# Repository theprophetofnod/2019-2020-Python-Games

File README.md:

# 2019-2020-Python-Games
# Ian started this on 1/15/2019. The end date should be 1/15/2020. If any one finds this after that date please terminate this repositories

# Example Code - Is the code that I am using to learn Python

# CorwRath - Is the name of the finsh product of my game.

# Test Code - Is the unfinshed code that I am working on.

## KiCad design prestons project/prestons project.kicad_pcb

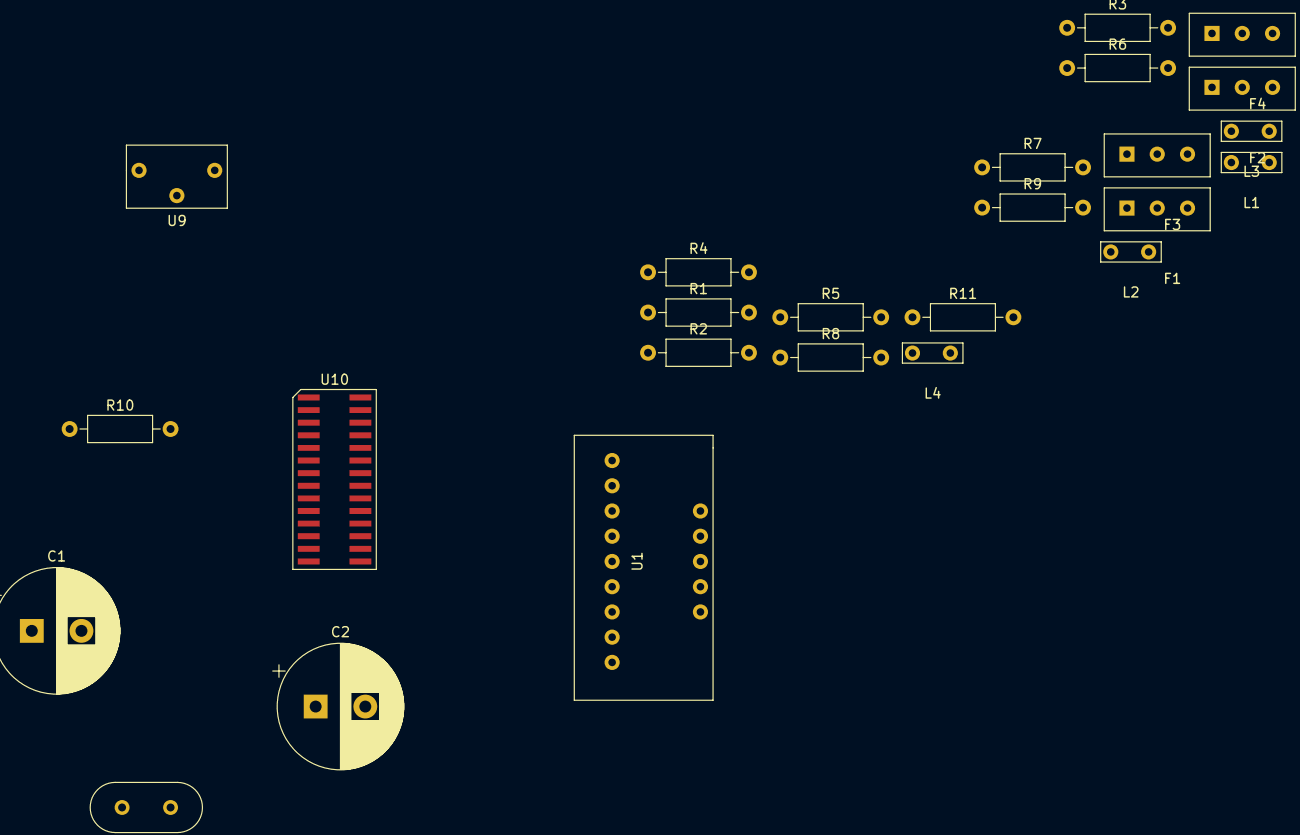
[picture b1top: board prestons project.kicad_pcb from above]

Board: 2 copper layers, 25 parts (0 on the bottom side), 22 nets, no tracks yet.

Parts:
C1: 18pF; CP_Radial_D12.5mm_P5.00mm
C2: 18Pf; CP_Radial_D12.5mm_P5.00mm
F1, F2, F3, F4: FQP30N06L; gatway_switch
L1, L2, L3, L4: load
R1, R2: 330R; R_Axial_DIN0207_L6.3mm_D2.5mm_P10.16mm_Horizontal
R3, R4, R5, R6, R7, R8, R9: 330; R_Axial_DIN0207_L6.3mm_D2.5mm_P10.16mm_Horizontal
R10: 2K; R_Axial_DIN0207_L6.3mm_D2.5mm_P10.16mm_Horizontal
R11: 10K; R_Axial_DIN0207_L6.3mm_D2.5mm_P10.16mm_Horizontal
U1: lsm9ds1
U9: LM3171; lm3171
U10: Atmega328; SOIC-28
Y1: 16MH Crystal oscillator; Crystal_HC49-U_Vertical

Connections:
/V1: R1.2, U10.15
/V2: R3.2, U10.16
/V3: R5.2, U10.17
/V4: R7.2, U10.12
/Vo: U10.7, U10.20
GND: C1.2, C2.2, F1.2, F2.2, F3.2, F4.2, R2.2, R4.2, R6.2, R8.2, R10.2, U1.3, U10.8, U10.22
unnamed: C1.1, U10.9, Y1.2
unnamed: C2.1, U10.10, Y1.1
unnamed: F1.1, L1.1
unnamed: F1.3, R1.1, R2.1
unnamed: F2.1, L2.1
unnamed: F2.3, R3.1, R4.1
unnamed: F3.1, L3.1
unnamed: F3.3, R5.1, R6.1
unnamed: F4.1, L4.1
unnamed: F4.3, R7.1, R8.1
unnamed: L1.2, L2.2, L3.2, L4.2
unnamed: R9.2, R10.1
unnamed: R11.1, U10.1
unnamed: R9.1, R11.2, U1.1
unnamed: U1.4, U10.28
unnamed: U1.5, U10.27

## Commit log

2019-01-16 Create learning how to code python games
2019-01-16 Update learning how to code python games
2019-01-16 Rename learning how to code python games to lC:\Users\ian\Desktop\python folder
2019-01-16 Update and rename learning how to code python games to Read Me
2019-01-16 Create Example folder
2019-01-16 Create Read Me
2019-01-16 Update Read Me
2019-07-11 Create police cart
